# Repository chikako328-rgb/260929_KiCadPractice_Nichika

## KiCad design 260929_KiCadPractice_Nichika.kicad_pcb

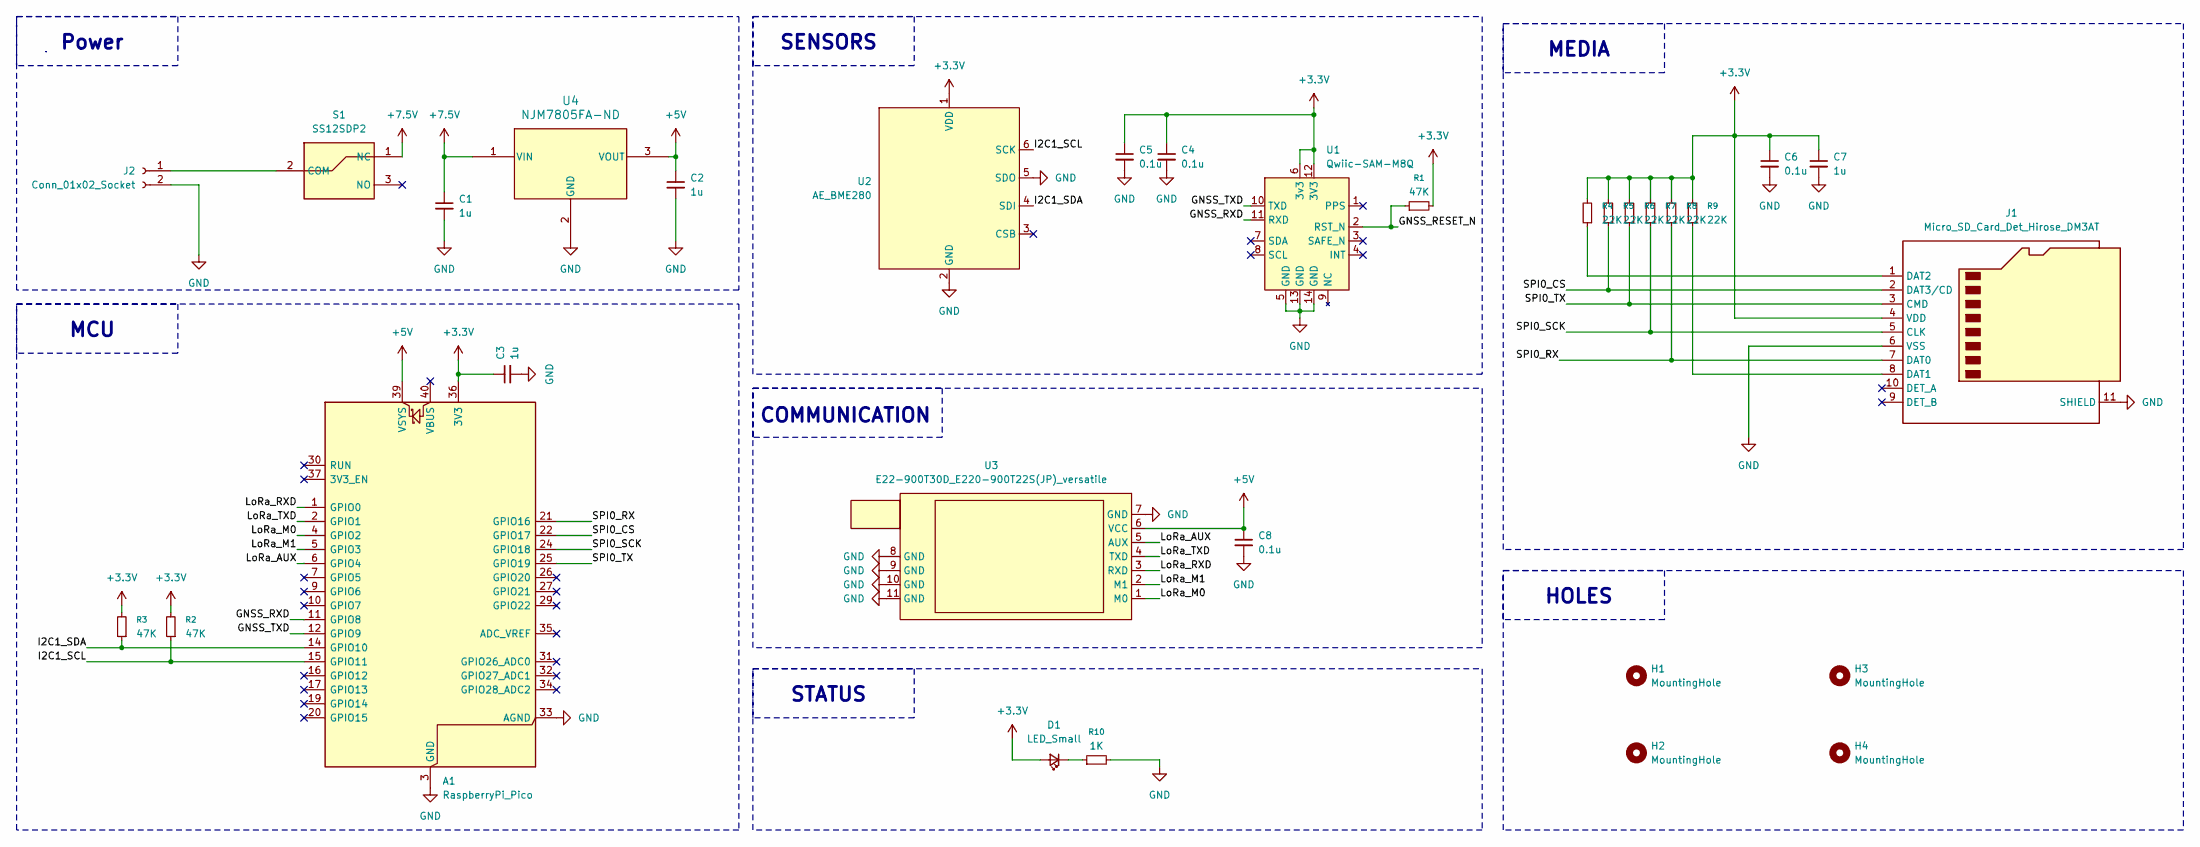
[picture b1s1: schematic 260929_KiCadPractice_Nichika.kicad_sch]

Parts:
A1: RaspberryPi_Pico; RaspberryPi_Pico_Common_Unspecified
C1, C2, C3, C7: 1u; C_0603_1608Metric_Pad1.08x0.95mm_HandSolder
C4, C5, C6, C8: 0.1u; C_0603_1608Metric_Pad1.08x0.95mm_HandSolder
D1: LED_Small; LED_D5.0mm
H1, H2, H3, H4: MountingHole; MountingHole_2.2mm_M2_ISO7380
J1: Micro_SD_Card_Det_Hirose_DM3AT; microSD_HC_Hirose_DM3AT-SF-PEJM5
J2: Conn_01x02_Socket; JST_XH_S2B-XH-A_1x02_P2.50mm_Horizontal
R1, R2, R3: 47K; R_0603_1608Metric_Pad0.98x0.95mm_HandSolder
R4, R5, R6, R7, R8, R9: 22K; R_0603_1608Metric_Pad0.98x0.95mm_HandSolder
R10: 1K; R_0603_1608Metric_Pad0.98x0.95mm_HandSolder
S1: SS12SDP2; Mouser Part Number 633-SS12SDP2
U1: Qwiic-SAM-M8Q; Qwiic_SAM-M8Q
U2: AE_BME280
U3: E22-900T30D_E220-900T22S(JP)_versatile
U4: NJM7805FA-ND; TO-220F-3_Vertical

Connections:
+3.3V: A1.36 (3V3), C3.1, C4.1, C5.1, C6.1, C7.1, D1.2 (A), J1.4 (VDD), R1.2, R2.2, R3.2, R4.2, R5.2, R6.2, R7.2, R8.2, R9.2, U1.6 (3v3), U1.12 (3V3), U2.1 (VDD)
+5V: A1.39 (VSYS), C2.1, C8.1, U3.6 (VCC), U4.3 (VOUT)
+7.5V: C1.1, S1.1 (NC), U4.1 (VIN)
/GNSS_RESET_N: R1.1, U1.2 (RST_N)
/GNSS_RXD: A1.11 (GPIO8), U1.11 (RXD)
/GNSS_TXD: A1.12 (GPIO9), U1.10 (TXD)
/I2C1_SCL: A1.15 (GPIO11), R2.1, U2.6 (SCK)
/I2C1_SDA: A1.14 (GPIO10), R3.1, U2.4 (SDI)
/LoRa_AUX: A1.6 (GPIO4), U3.5 (AUX)
/LoRa_M0: A1.4 (GPIO2), U3.1 (M0)
/LoRa_M1: A1.5 (GPIO3), U3.2 (M1)
/LoRa_RXD: A1.1 (GPIO0), U3.3 (RXD)
/LoRa_TXD: A1.2 (GPIO1), U3.4 (TXD)
/SPI0_CS: A1.22 (GPIO17), J1.2 (DAT3/CD), R5.1
/SPI0_RX: A1.21 (GPIO16), J1.7 (DAT0), R8.1
/SPI0_SCK: A1.24 (GPIO18), J1.5 (CLK), R7.1
/SPI0_TX: A1.25 (GPIO19), J1.3 (CMD), R6.1
GND: A1.3 (GND), A1.8 (GND), A1.13 (GND), A1.18 (GND), A1.23 (GND), A1.28 (GND), A1.33 (AGND), A1.38 (GND), C1.2, C2.2, C3.2, C4.2, C5.2, C6.2, C7.2, C8.2, J1.6 (VSS), J1.11 (SHIELD), J2.2, R10.2, U1.5 (GND), U1.13 (GND), U1.14 (GND), U2.2 (GND), U2.5 (SDO), U3.7 (GND), U3.8 (GND), U3.9 (GND), U3.10 (GND), U3.11 (GND), U4.2 (GND)
unnamed: D1.1 (K), R10.1
unnamed: J1.8 (DAT1), R9.1
unnamed: J1.1 (DAT2), R4.1
unnamed: J2.1, S1.2 (COM)

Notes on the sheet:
HOLES
COMMUNICATION
SENSORS
MCU
MEDIA
STATUS
Power

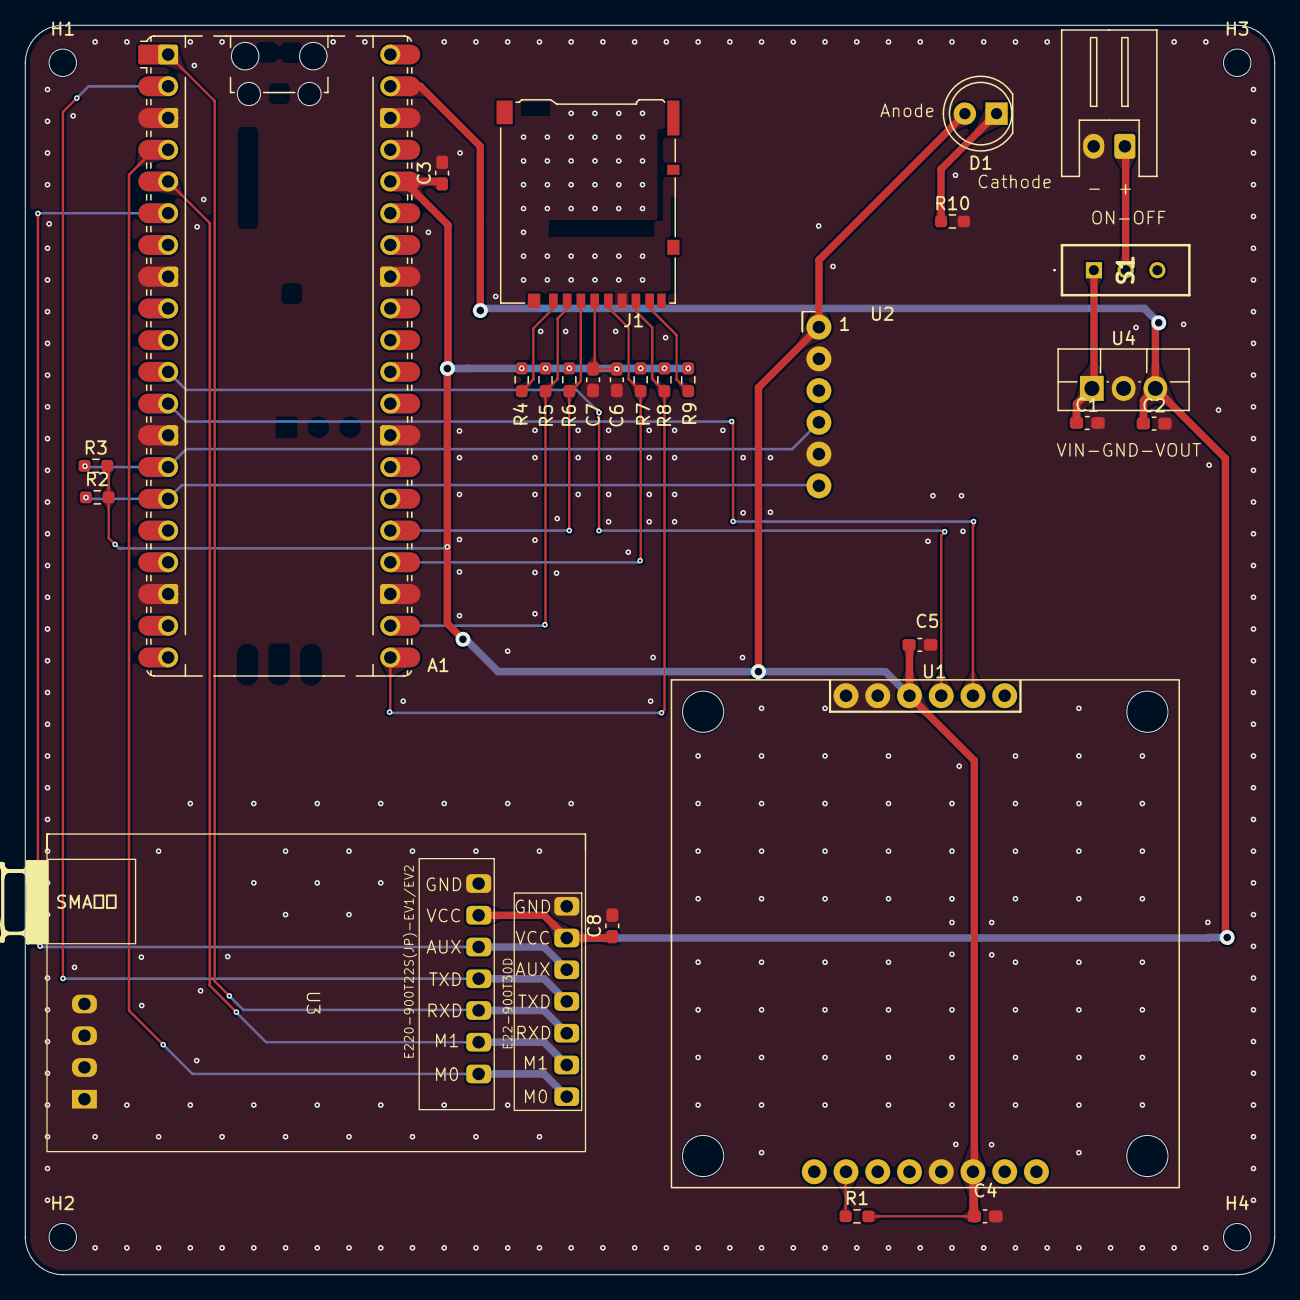
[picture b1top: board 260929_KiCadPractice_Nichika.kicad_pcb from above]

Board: 2 copper layers, 100.0 x 100.0 mm, 31 parts (0 on the bottom side), 22 nets.
